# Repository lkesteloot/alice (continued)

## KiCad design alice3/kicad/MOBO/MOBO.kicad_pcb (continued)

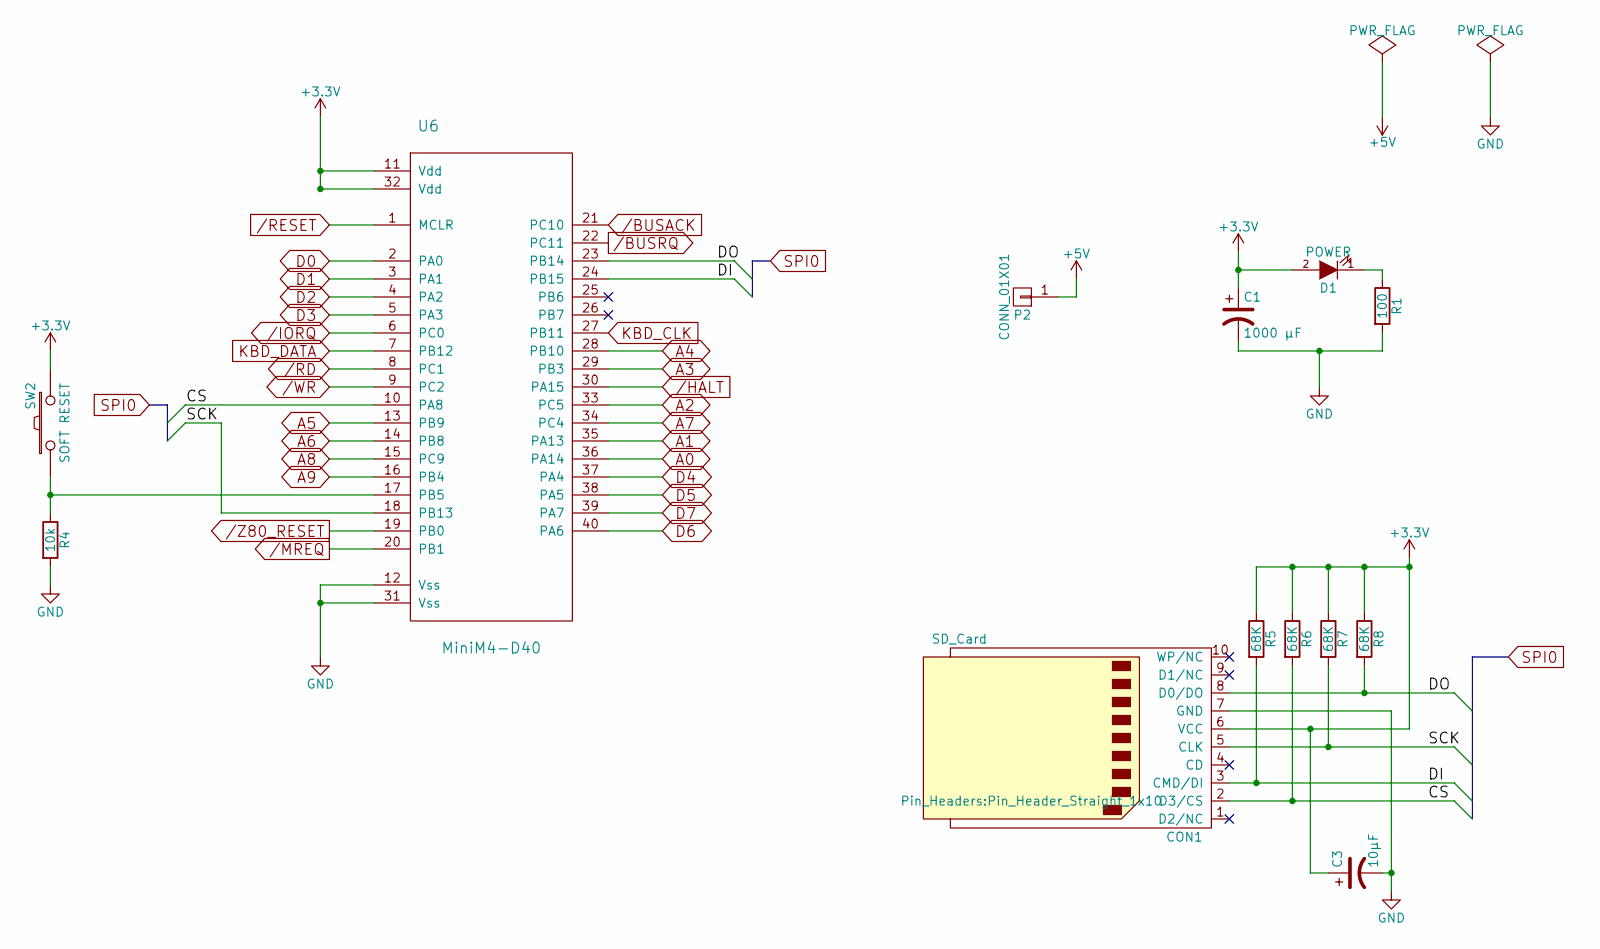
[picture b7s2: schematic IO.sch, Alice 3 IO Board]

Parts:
C1: 1000 µF; C_Radial_D8_L11.5_P3.5
C3: 10µF; C_Radial_D5_L11_P2.5
CON1: SD_Card; Pin_Header_Straight_1x10
D1: POWER; LED-5MM
P2: CONN_01X01; Pin_Header_Straight_1x01
R1: 100; Resistor_Horizontal_RM10mm
R4: 10k; Resistor_Horizontal_RM10mm
R5, R6, R7, R8: 68K; Resistor_Horizontal_RM10mm
SW2: SOFT RESET; SW_PUSH_SMALL
U6: MiniM4-D40; DIP-40_W15.24mm

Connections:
+5V: P2.1; also elsewhere on the board
/BUSACK: U6.21 (PC10); also elsewhere on the board
/BUSRQ: U6.22 (PC11); also elsewhere on the board
/HALT: U6.30 (PA15); also elsewhere on the board
/IO/CS: CON1.2 (D3/CS), R6.2, U6.10 (PA8)
/IO/DI: CON1.3 (CMD/DI), R5.2, U6.24 (PB15)
/IO/DO: CON1.8 (D0/DO), R8.2, U6.23 (PB14)
/IO/SCK: CON1.5 (CLK), R7.2, U6.18 (PB13)
/IORQ: U6.6 (PC0); also elsewhere on the board
/MREQ: U6.20 (PB1); also elsewhere on the board
/RD: U6.8 (PC1); also elsewhere on the board
/RESET: U6.1 (MCLR); also elsewhere on the board
/WR: U6.9 (PC2); also elsewhere on the board
/Z80_RESET: U6.19 (PB0); also elsewhere on the board
A0: U6.36 (PA14); also elsewhere on the board
A1: U6.35 (PA13); also elsewhere on the board
A2: U6.33 (PC5); also elsewhere on the board
A3: U6.29 (PB3); also elsewhere on the board
A4: U6.28 (PB10); also elsewhere on the board
A5: U6.13 (PB9); also elsewhere on the board
A6: U6.14 (PB8); also elsewhere on the board
A7: U6.34 (PC4); also elsewhere on the board
A8: U6.15 (PC9); also elsewhere on the board
A9: U6.16 (PB4); also elsewhere on the board
D0: U6.2 (PA0); also elsewhere on the board
D1: U6.3 (PA1); also elsewhere on the board
D2: U6.4 (PA2); also elsewhere on the board
D3: U6.5 (PA3); also elsewhere on the board
D4: U6.37 (PA4); also elsewhere on the board
D5: U6.38 (PA5); also elsewhere on the board
D6: U6.40 (PA6); also elsewhere on the board
D7: U6.39 (PA7); also elsewhere on the board
GND: C1.2, C3.2, CON1.7 (GND), R1.2, R4.2, U6.12 (Vss), U6.31 (Vss); also elsewhere on the board
KBD_CLK: U6.27 (PB11); also elsewhere on the board
KBD_DATA: U6.7 (PB12); also elsewhere on the board
unnamed: D1.1 (K), R1.1
unnamed: R4.1, SW2.1, U6.17 (PB5)

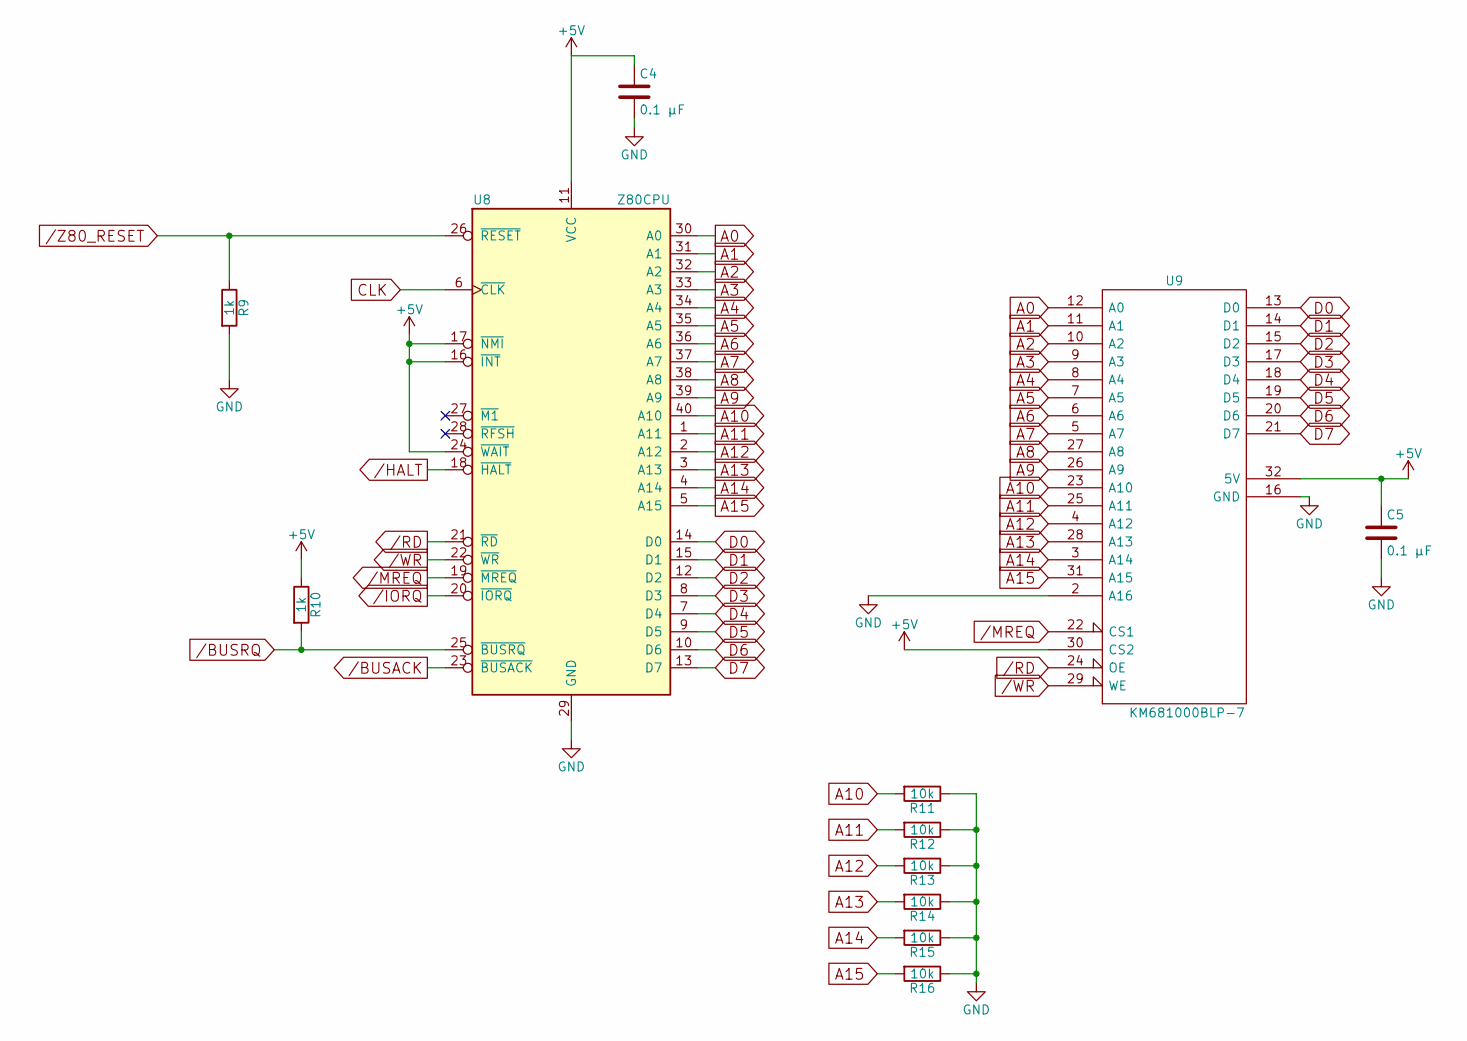
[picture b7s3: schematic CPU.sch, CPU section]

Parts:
C4, C5: 0.1 µF; C_Disc_D6_P5
R9, R10: 1k; Resistor_Horizontal_RM10mm
R11, R12, R13, R14, R15, R16: 10k; Resistor_Horizontal_RM10mm
U8: Z80CPU; DIP-40_W15.24mm
U9: KM681000BLP-7; DIP-32_W15.24mm

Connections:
/BUSACK: U8.23 (~BUSACK~); also elsewhere on the board
/BUSRQ: R10.2, U8.25 (~BUSRQ~); also elsewhere on the board
/HALT: U8.18 (~HALT~); also elsewhere on the board
/IORQ: U8.20 (~IORQ~); also elsewhere on the board
/MREQ: U8.19 (~MREQ~), U9.22 (CS1); also elsewhere on the board
/RD: U8.21 (~RD~), U9.24 (OE); also elsewhere on the board
/WR: U8.22 (~WR~), U9.29 (WE); also elsewhere on the board
/Z80_RESET: R9.1, U8.26 (~RESET~); also elsewhere on the board
A0: U8.30 (A0), U9.12 (A0); also elsewhere on the board
A1: U8.31 (A1), U9.11 (A1); also elsewhere on the board
A2: U8.32 (A2), U9.10 (A2); also elsewhere on the board
A3: U8.33 (A3), U9.9 (A3); also elsewhere on the board
A4: U8.34 (A4), U9.8 (A4); also elsewhere on the board
A5: U8.35 (A5), U9.7 (A5); also elsewhere on the board
A6: U8.36 (A6), U9.6 (A6); also elsewhere on the board
A7: U8.37 (A7), U9.5 (A7); also elsewhere on the board
A8: U8.38 (A8), U9.27 (A8); also elsewhere on the board
A9: U8.39 (A9), U9.26 (A9); also elsewhere on the board
A10: R11.2, U8.40 (A10), U9.23 (A10)
A11: R12.2, U8.1 (A11), U9.25 (A11)
A12: R13.2, U8.2 (A12), U9.4 (A12)
A13: R14.2, U8.3 (A13), U9.28 (A13)
A14: R15.2, U8.4 (A14), U9.3 (A14)
A15: R16.2, U8.5 (A15), U9.31 (A15)
CLK: U8.6 (~CLK~); also elsewhere on the board
D0: U8.14 (D0), U9.13 (D0); also elsewhere on the board
D1: U8.15 (D1), U9.14 (D1); also elsewhere on the board
D2: U8.12 (D2), U9.15 (D2); also elsewhere on the board
D3: U8.8 (D3), U9.17 (D3); also elsewhere on the board
D4: U8.7 (D4), U9.18 (D4); also elsewhere on the board
D5: U8.9 (D5), U9.19 (D5); also elsewhere on the board
D6: U8.10 (D6), U9.20 (D6); also elsewhere on the board
D7: U8.13 (D7), U9.21 (D7); also elsewhere on the board
GND: C4.2, C5.2, R9.2, R11.1, R12.1, R13.1, R14.1, R15.1, R16.1, U8.29 (GND), U9.2 (A16), U9.16 (GND); also elsewhere on the board

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
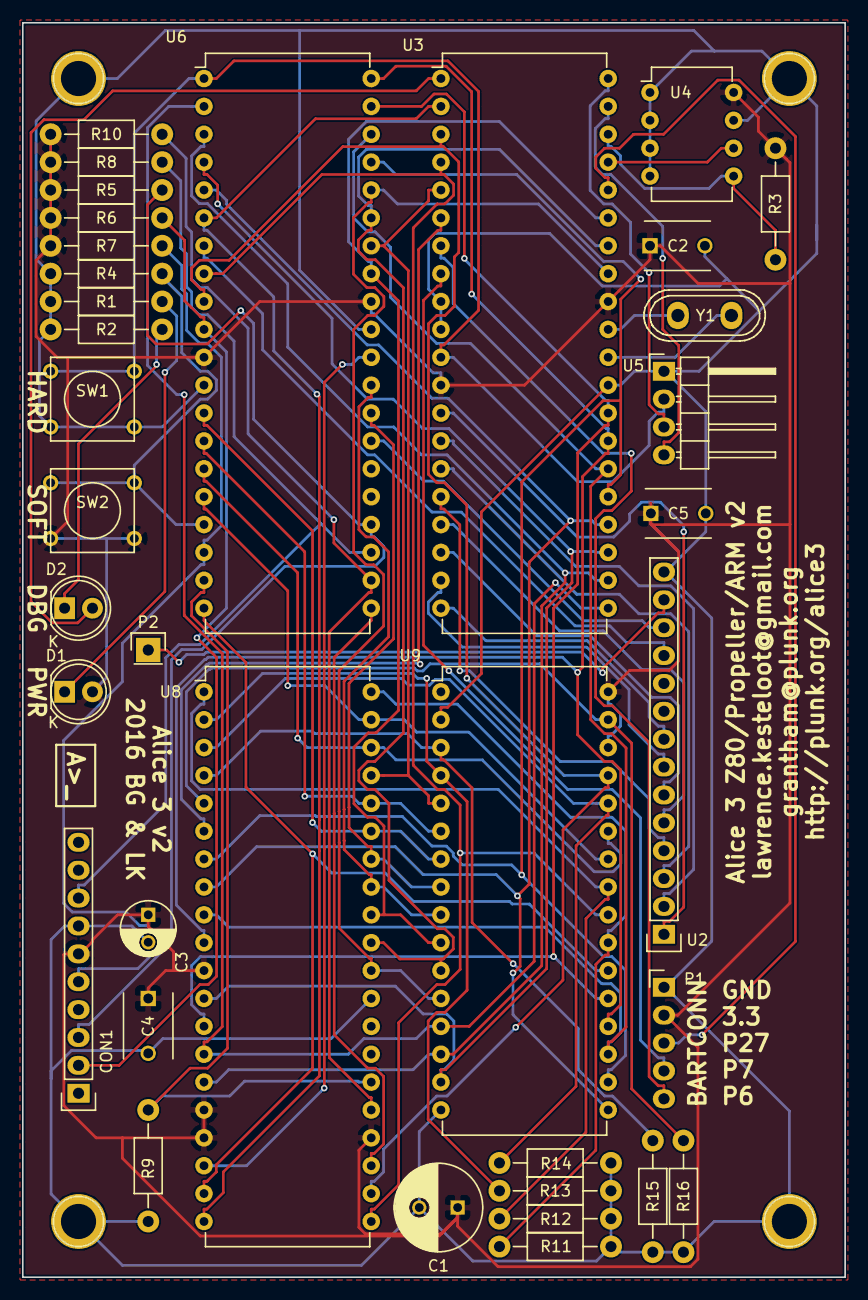
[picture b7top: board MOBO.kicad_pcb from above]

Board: 2 copper layers, 74.9 x 114.3 mm, 40 parts (0 on the bottom side), 64 nets.

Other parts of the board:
HOLE1, HOLE2, HOLE3, HOLE4: 1pin

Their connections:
GND: HOLE1.1, HOLE2.1, HOLE3.1, HOLE4.1; also elsewhere on the board

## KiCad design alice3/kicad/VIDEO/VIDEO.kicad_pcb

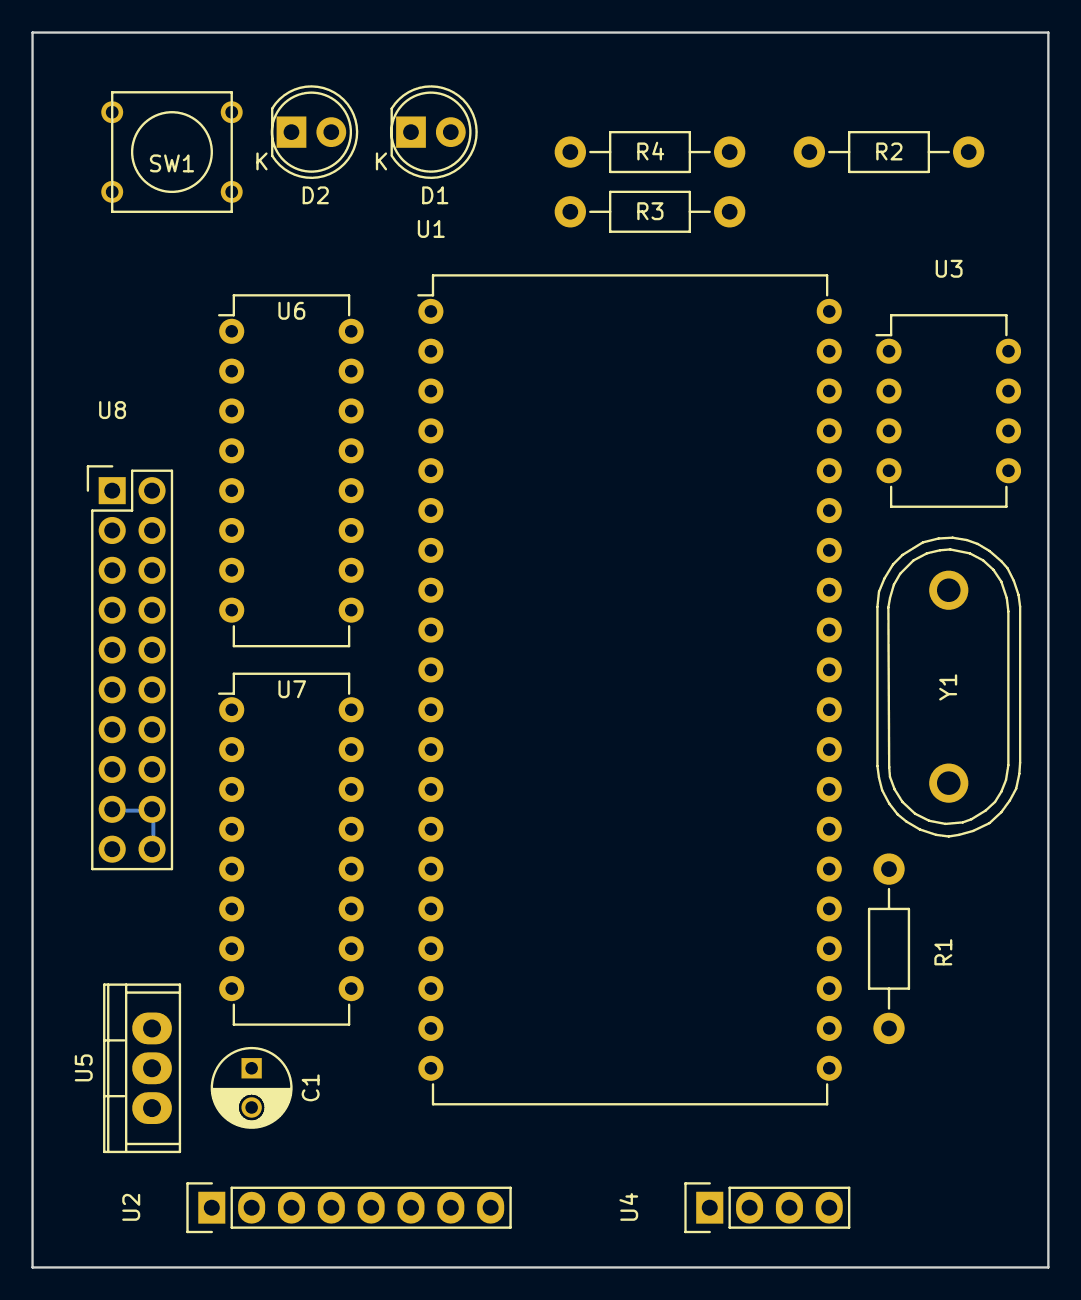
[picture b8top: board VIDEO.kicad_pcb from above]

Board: 2 copper layers, 64.8 x 78.7 mm, 17 parts (0 on the bottom side), 43 nets.

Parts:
C1: 1000 µF; C_Radial_D5_L6_P2.5
D1: POWER; LED-5MM
D2: DEBUG; LED-5MM
R1: 10K; Resistor_Horizontal_RM10mm
R2: 10k; Resistor_Horizontal_RM10mm
R3, R4: 100; Resistor_Horizontal_RM10mm
SW1: RESET; SW_PUSH_SMALL
U1: Propeller_P8X32A-D40; DIP-40_W25.4mm
U2: VGA_daughter_board; Pin_Header_Straight_1x08
U3: 24LC256; DIP-8_W7.62mm
U4: Propeller_Plug; Pin_Header_Straight_1x04
U5: LM2937-3.3; TO-220
U6, U7: 74HC4050; DIP-16_W7.62mm
U8: Alice_3_bus; Pin_Header_Straight_2x10
Y1: 5 MHz; Crystal_HC48-U_Vertical

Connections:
+3V3: C1.1, D1.2, R1.1, R2.1, U1.12, U1.32, U3.8, U5.3, U6.1, U7.1
+5V: U5.1, U8.2, U8.10
//IORQ: U1.33, U7.10
//WR: U1.34, U7.12
/A7: U1.35, U7.6
/D0: U1.21, U6.2
/D1: U1.22, U6.4
/D2: U1.23, U6.6
/D3: U1.24, U6.10
/D4: U1.25, U6.12
/D5: U1.26, U6.15
/D6: U1.27, U7.2
/D7: U1.28, U7.4
GND: C1.2, R3.2, R4.2, SW1.2, U1.9, U1.10, U1.29, U3.1, U3.2, U3.3, U3.4, U3.7, U4.1, U5.2, U6.8, U7.8, U7.14, U8.1, U8.20
unnamed: D1.1, R3.1
unnamed: D2.1, R4.1
unnamed: D2.2, U1.1
unnamed: R1.2, SW1.1, U1.11, U4.2
unnamed: R2.2, U1.38, U3.5
unnamed: U1.13, U2.1
unnamed: U1.14, U2.2
unnamed: U1.15, U2.3
unnamed: U1.16, U2.4
unnamed: U1.17, U2.5
unnamed: U1.18, U2.6
unnamed: U1.19, U2.7
unnamed: U1.20, U2.8
unnamed: U1.30, Y1.1
unnamed: U1.31, Y1.2
unnamed: U1.37, U3.6
unnamed: U1.39, U4.4
unnamed: U1.40, U4.3
unnamed: U6.3, U8.11
unnamed: U6.5, U8.12
unnamed: U6.7, U8.13
unnamed: U6.9, U8.14
unnamed: U6.11, U8.15
unnamed: U6.14, U8.16
unnamed: U7.3, U8.17
unnamed: U7.5, U8.18
unnamed: U7.7, U8.19
unnamed: U7.9, U8.9
unnamed: U7.11, U8.8

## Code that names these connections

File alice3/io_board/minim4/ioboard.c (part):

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#define KBD_BIT_COUNT 11

volatile short kbd_bits = 0;
volatile unsigned short kbd_data = 0;
volatile char up_key_flag = 0;
volatile char kbd_shift_status = 0;
volatile char kbd_alt_status = 0;
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        } else {
            queue_enq(&kbd_queue.q, (kbd_data >> 1) & 0xff);
        }
        kbd_data = 0;
        kbd_bits = 0;
    }
}
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#define MEMORY_DELAY_MICROS     10
#define IO_DELAY_MICROS     2

// IORQ, RD, WR, and A7 are specially implemented to be on one GPIO register
// in order to quickly determine if IO is being read or written

#define BUS_SIGNAL_CHECK_PORT GPIOC
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
        __asm__ volatile("" ::: "memory"); // Force all memory operations before to come before and all after to come after.

        while((BUS_SIGNAL_CHECK_PORT->IDR & BUS_RD_PIN_MASK) == BUS_RD_ACTIVE); /* busy wait for RD to rise */
        __asm__ volatile("" ::: "memory"); // Force all memory operations before to come before and all after to come after.
        BUS_set_DATA_as_input();

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
        __asm__ volatile("" ::: "memory"); // Force all memory operations before to come before and all after to come after.

        while((BUS_SIGNAL_CHECK_PORT->IDR & BUS_RD_PIN_MASK) == BUS_RD_ACTIVE); /* busy wait for RD to rise */
        __asm__ volatile("" ::: "memory"); // Force all memory operations before to come before and all after to come after.
        BUS_set_DATA_as_input();

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    HAL_NVIC_SetPriority(EXTI2_IRQn, 0, 0);
    HAL_NVIC_EnableIRQ(EXTI2_IRQn);

    // IORQ and A7 are port C pins 0, 4, as inputs
    GPIO_InitStruct.Pin = BUS_IORQ_PIN_MASK | BUS_A7_PIN_MASK;
    GPIO_InitStruct.Mode = GPIO_MODE_INPUT;
    GPIO_InitStruct.Pull = GPIO_NOPULL;
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#define RESET_BUTTON_IRQn EXTI9_5_IRQn
#define RESET_BUTTON_DELAY_MS 10

#define Z80_RESET_PORT GPIOB
#define Z80_RESET_PIN_MASK GPIO_PIN_0
#define Z80_RESET_ACTIVE 0
#define Z80_RESET_INACTIVE Z80_RESET_PIN_MASK
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    GPIO_InitStruct.Mode = GPIO_MODE_OUTPUT_PP;
    GPIO_InitStruct.Pull = GPIO_NOPULL;
    GPIO_InitStruct.Speed = GPIO_SPEED_FREQ_LOW;
    HAL_GPIO_Init(Z80_RESET_PORT, &GPIO_InitStruct); 
    HAL_GPIO_WritePin(Z80_RESET_PORT, Z80_RESET_PIN_MASK, Z80_RESET_ACTIVE);
    gZ80IsInRESET = 1;
}

void BUS_reset_start()
{
    HAL_GPIO_WritePin(Z80_RESET_PORT, Z80_RESET_PIN_MASK, Z80_RESET_ACTIVE);
    gZ80IsInRESET = 1;
    delay_ms(Z80_RESET_DURATION_MS);
}
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void BUS_reset_finish()
{
    gZ80IsInRESET = 0;
    HAL_GPIO_WritePin(Z80_RESET_PORT, Z80_RESET_PIN_MASK, Z80_RESET_INACTIVE);
}

volatile int gResetTheZ80 = 0;
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}

#define PROP_READY_PIN_MASK GPIO_PIN_14
#define PROP_READY_PORT GPIOC

void VIDEO_init()
{
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    GPIO_InitStruct.Mode = GPIO_MODE_INPUT;
    GPIO_InitStruct.Pull = GPIO_PULLUP;
    GPIO_InitStruct.Speed = GPIO_SPEED_FREQ_LOW;
    HAL_GPIO_Init(PROP_READY_PORT, &GPIO_InitStruct); 
}

void VIDEO_wait()
{
    int started = HAL_GetTick();
    int then = HAL_GetTick();
    while(HAL_GPIO_ReadPin(PROP_READY_PORT, PROP_READY_PIN_MASK)) {
        int now = HAL_GetTick();
        if(now - then > 500) {
            printf("Waited 500 more milliseconds for PROP_READY\n");
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
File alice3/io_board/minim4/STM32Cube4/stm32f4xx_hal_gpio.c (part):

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        pins).
  
    (#) The LSE oscillator pins OSC32_IN and OSC32_OUT can be used as general purpose 
        (PC14 and PC15, respectively) when the LSE oscillator is off. The LSE has 
        priority over the GPIO function.
  
    (#) The HSE oscillator pins OSC_IN/OSC_OUT can be used as 
        general purpose PH0 and PH1, respectively, when the HSE oscillator is off. 
        The HSE has priority over the GPIO function.
  
  @endverbatim
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
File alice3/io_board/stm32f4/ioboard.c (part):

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        } else if(strcmp(gMonitorCommandLine, "bus") == 0) {

            printf("RESET %s\n", HAL_GPIO_ReadPin(BUS_RESET_PORT, BUS_RESET_PIN_MASK) ? "high" : "low");
            printf("HALT %s\n", HAL_GPIO_ReadPin(BUS_HALT_PORT, BUS_HALT_PIN_MASK) ? "high" : "low");
            printf("IORQ %s\n", HAL_GPIO_ReadPin(BUS_IORQ_PORT, BUS_IORQ_PIN_MASK) ? "high" : "low");
            printf("MREQ %s\n", HAL_GPIO_ReadPin(BUS_MREQ_PORT, BUS_MREQ_PIN_MASK) ? "high" : "low");
            printf("RD %s\n", HAL_GPIO_ReadPin(BUS_RD_PORT, BUS_RD_PIN_MASK) ? "high" : "low");
            printf("WR %s\n", HAL_GPIO_ReadPin(BUS_WR_PORT, BUS_WR_PIN_MASK) ? "high" : "low");
            printf("BUSRQ %s\n", HAL_GPIO_ReadPin(BUS_BUSRQ_PORT, BUS_BUSRQ_PIN_MASK) ? "high" : "low");
            printf("BUSAK %s\n", HAL_GPIO_ReadPin(BUS_BUSAK_PORT, BUS_BUSAK_PIN_MASK) ? "high" : "low");

        } else if(strcmp(gMonitorCommandLine, "low128") == 0) {
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
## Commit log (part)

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2017-04-15 Fix various bugs in FIFO code.
2017-04-15 Can increment in memtool.
2017-04-15 Convert image to 32bits before accessing
2017-04-16 Pretty stable frame buffer.
2017-04-16 Double size of FIFO to avoid underrun.
2017-04-16 Encapsulate touchscreen in its own unit
2017-04-16 Add beginnings of events on hardware
2017-04-16 Add ERROR prints on unexpected conditions
2017-04-17 Move flush so gl.c is not dependent on network
2017-04-17 Add platform.mk file for choosing implementation
    Edit platform.mk to change the implementaiton of the rasterizer and events.
2017-04-17 More careful LCD pixel output.
2017-04-19 Convert output to G's
2017-04-24 Add second memory interface.
2017-04-24 Modify memtool to support 64-bit writes and reads.
2017-04-24 Protocol test program.
2017-04-24 Draw bounding box of triangle.
2017-04-24 Turn of debug printf and usleep() now that we block on swap buffers.
2017-04-25 Respect triangle color; display count of unhandled commands.
2017-04-25 Make GPU command buffer - not tested
2017-04-26 Correct check for mmap() failure (not compiled or tested).
2017-04-26 Change DEBUG_PRINT to undef
2017-04-27 Reset buffer after each frame.
2017-04-27 Put image in both framebuffers
    Make new put_image function.
    Put the fipImage in both framebuffers that may be scanned out.
    Center image correctly in dimensions less than the framebuffer size.
2017-04-27 Add a utility to save the framebuffers as images
    Save off each framebuffer using FreeImagePlus.
    FIP will automatically use an encoder matching the filename extension entered.
    e.g. sudo alice4save framebuffer0.png framebuffer1.jpg # not that you'd do this, but it works
    Hardcode the framebuffer location, rowbytes, and bpp for convenience.
2017-04-28 Spin triangle more slowly in the test.
2017-04-28 Disable networking in Arena, it doesn't compile on the embedded Linux.
2017-04-29 Bigger FB FIFO and latch the debug text.
2017-04-30 Compare open against -1 to detect failure
    OMG, this is kind of embarrassing.
2017-04-30 Fix tied evaluator record and read
    Fix cut-and-paste error in tied evaluator loop - set loop variable k but did not use it to read evaluator device
    Fix events_tie() - was not using the correct array index
2017-05-01 Software side of pattern.
2017-05-01 Add code to parse PATTERN (untested)
2017-05-01 Implement patterns in FPGA.
2017-05-02 Add pattern test to protocol program.
2017-05-02 Add optimization to all Makefiles
    This change boosts logo's CPU-only frame rate from 25 frames per second to 95.
2017-05-03 Double-buffer the command stream
    If "double_buffer_commands" is set to 0, commands are written directly to the GPU memory buffer for commands. (Therefore no additional commands can be safely written to the buffer until the GPU has f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
    If "double_buffer_commands" is set to 1, commands are written directly to a separate "staging" memory buffer. "swap" waits until any previous GPU work is complete, meaning the GPU buffer can be writt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
    N.B. By default now set double_buffer_commands to 1. It is a const variable me
2017-05-03 Expose front buffer bit.
2017-05-04 Add frame stats per-frame and averaged over a second
    PRINT_FRAME_STATS=1 will print ms for some portions of the frame every second.
    PRINT_FRAME_STATS=2 will print ms for some portions of the frame every frame.
2017-05-04 Program to pulse LCD backlight.
2017-05-04 Fix bounding box calculation.
2017-05-04 Modify fpgasim to do more efficient color interpolation.
2017-05-04 Print time spent waiting on raster finish
2017-05-04 Revert accidental change to platform makefile.
2017-05-04 Write overlay in single-bit red so as to not disturb the LCD. Need to investigate why this is necessary.
2017-05-05 add -lm for Linux build
2017-05-08 Tilt test over VNC
    Prints "TILT_VALID" and tilt valuators when tilt is within accurate ranges.
    Prints "TILT_INVALID" and does not print valuators when tilt is out of range.
2017-05-13 Add two stages to the reciprocal (from 4 to 6) to eliminate timing warnings.
    Fixes #34.
2017-05-17 Add modes for just ramp and for delaying all bits
    Change size to 800x480 so that output matches Alice 4 display
    - notably the ramp can be loaded into Alice 4 display to illustrate issues
    "make" creates all three images.
    Provide "--all8bits" to delay all 8 bits of the color, showing close to what Brad sees.
    Provide "--justramp" to output the color ramp with no output effect.
2017-05-18 Add Z buffer test to protocol.cpp.
2017-05-22 DISPLAY_ENABLE -> DATA_ENABLE
2017-05-22 Add some boards and chips we're using
    Adafruit Bluefruit LE SPI
    Adafruit L3GD20H breakout
    Adafruit PowerBoost 1000c
    STM STMPE811
2017-05-22 Add memory controller ports for Z.
2017-05-24 Add write FIFO and use it for color.
2017-05-24 Interpolate Z.
2017-05-24 Move i2c functions into utility module
2017-05-24 Accelerometer module
2017-05-24 Fix math error converting radians to degres
2017-05-24 Smooth accelerometer with exponential decay
    Add (current sensor reading * (1 - decay)) to (old * decay).
    Smoothing helps somewhat with decay = .5. Decay = .8 looks a lot better but loses rapid motion.
    Committing decay = 0.5.
2017-05-25 Clean up Verilog code.
2017-05-26 Fix Z buffer artifacts. Fixes #13.
2017-05-26 Add stats to protocol test.
2017-05-26 Clear Z in protocol test.
2017-05-28 Remove test code.
2017-05-28 Add notes for test fifo.
2017-05-29 Speed up rasterization. Fixes #40.
2017-05-29 Fix use of fifo.empty in read fifo.
2017-06-02 Always spin object slowly, fix Z
    Remove call to gversion and machine-dependent Z setup.
    Use default Z function, back-to-front values for lsetdepth, and clear Z to far.
    Set "spin" to default to TRUE and spin 1/3 as fast as it was spinning.
2017-06-03 Add tilt
2017-06-04 Rasterize lines
2017-06-04 Rasterize lines more correctly
    Draw boxes that represent lines by extending line by linewidth along
    axis perpendicular to the line's major axis, resulting in parallelograms.
2017-06-04 Factor out libawesome.
2017-06-04 Add home support to protocol test program.
2017-06-04 Use one global Awesome
    Move struct definition into awesome.c.
    Keep one global Awesome instance in awesome.c.
    Remove all Awesome pointers from awesome functions.
    Fixup protocol test to match.
2017-06-04 Don't pass a pointer to an Awesome
2017-06-04 Warn if we skip a frame.
2017-06-04 Add Arena
2017-06-04 compile with networking
2017-06-04 Implement czclear(), fix #39
    Implement czclear in rasterizer interface and rasterizer implementations.
    In hardware_rasterizer, pass czclear to libawesome
    Use czclear in logo and jello (already used in bounce)
2017-06-04 Set ESC (Home) to exit only submenus in buttonfly
2017-06-04 Add ability to dump logo commands to a file. For #22.
2017-06-04 Add Make target for writing logo.bin to SD card.
2017-06-05 Add memory thrashing tool.
2017-06-11 Fix line endings for u-boot.txt.
2017-06-12 Re-enable double buffering of commands.
2017-06-12 Break up long thin triangles. For issue #17.
    Long thin (diagonal) triangles waste a lot of time in the
    rasterizer because we consider every point in the bounding
    box. With this change, if the ratio of triangle pixels
    to bounding box pixels is low, we tesselate the triangle.
    This halves the number of bounding box pixels (1.8m to 0.9m)
    at the slowest frame of buttonfly. (The bevel of the button
2017-06-12 Configure extra memory ports.
2017-06-16 add network events example in a comment
2017-06-16 fix array overrun
2017-06-16 Avoid divide by zero when displaying statistics.
2017-06-16 Don't start reading command buffer until we're ready.
2017-06-16 Bogus no-op changes by Quartus.
2017-07-15 Update overview page.
2017-07-15 Fix up Alice 2 docs.
2017-07-15 Load fonts over https.
2017-07-15 Use arabic numerals instead of roman ones for Alice version numbers.
2017-07-15 Add stub Alice 4 page.
2017-07-20 Disable blinking LED.
2017-07-26 Don't show arena instructions. Fixes #58.
2017-07-26 Add disabled code to split up lines.
2017-08-02 Add Makefile targets to start/stop service.
2017-08-03 IrisGL transformation and lighting benchmark
2017-08-04 Don't enable shutdown in Makefile.
2017-08-04 Dummy events in platform Makefile.
2017-08-05 Fix aspect ratio of ideas.
2017-08-05 Replace shutdown with ideas.
2017-08-06 Final flight changes to make it build.
2017-08-06 Fix flight warnings and clear bug in gl.
2017-08-08 Run the 747 by default in flight.
2017-08-09 Link to web page.
2017-08-09 Add secret menu.
2017-08-10 switch interaction to that of jello
2017-08-10 render all 6 walls with faceculling
2017-08-15 Big VCF West 2017 commit
    Terminal.spin: complete rewrite in prop asm, lots more codes handled,
    jump table used which should provide a good example for streamlining in
    the future
    Bus_interface.spin: better documentation at the top, added serial terminal
    mirroring but commented-out, added ay_allatonce handler, added ay_BEL
    Main.spin: added another row to the buffer for easier terminal scrolling
2017-08-15 Added JDCogSerial.spin to alice3/video_board/propeller directory since the alternative commented-out terminal code in Main.spin references it
2017-08-16 make CE2 high
2017-08-16 draft DABO2 PCB
2017-08-16 footprints
2017-08-17 increase SD speed to about 21MHz after init
2017-08-17 ARM fimware binary with faster SD access
2017-08-19 catch correct enum for WRITE_DMA
2017-08-19 implement ARM firmware for DMA READ and WRITE
2017-08-26 set up RFSH and WAIT signals correctly
2017-08-28 1st set MOBO schematic fixes for 1st PCBWay spin
    Various fixes for KiCAD messing up components
    Button on BOOT0
    No huge cap on power supply LED
    Discard RAM
    Route ARM to Z80 /WAIT and /RFSH
    Use "~" for active-low lines (shown in schematic by line above them)
2017-08-29 V4 improvements round 2
    Label buttons, LEDs, and connectors
    Delete footprints for deleted schematic parts
    Move microUSB jack and space out PS2, VGA connectors
    Position SMT Propeller crystal
    Change BOOT0 header to button
    Delete RAM
2017-08-29 consolidate all Z80 addr pins on one ARM port
2017-09-06 fix misspelling of "staging"
2017-09-07 constant current part FAN5333A/B
2017-09-07 integrate constant current driver, drop TFT Friend
2017-09-08 replace L3DG20H breakout with actual chip
2017-09-09 TPS61090 boost supply
2017-09-10 add source files for components
2017-09-11 run LIPO to STMPE811 ADC on IN0
2017-09-13 Add link to red button.
2017-09-13 Acrylic enclosure.
2017-09-13 l3gd20h qfn footprint
2017-09-13 first draft of layout
2017-09-14 add hidden PAD pins that are GND
2017-09-14 Second draft of layout
    Lawrence fixes to schematic
    Layout PCB
2017-09-16 remove R pulling PWREN to VBAT
2017-09-17 one more draft layout; better 3v3 plane
2017-09-18 add SMD 1206 testpoint pad footprint
2017-09-18 Hopefully near final layout
2017-09-27 Add jac library including large hole
2017-09-29 add ideas
2017-09-29 rotate 180 degrees
2017-10-10 Fix up WaveDrom for write FIFO.
2017-10-12 Minor tweaks to write-up.
2017-10-16 Better motivation for area reciprocal.
2017-10-16 Get flight to compile on Alice 4.
2017-10-16 Slower accelerator decay.
2017-10-16 Fix secret menu.
2017-10-16 Re-enable culling, implement correctly
    Ideas now works and the bounce models (except for doughnut?!) work properly and at full rate
2017-10-22 Start Verilator simulation integration.
2017-10-22 Add Frame buffer to Verilator.
2017-10-24 Add and link placeholder for libgl page
2017-10-25 Add more about libgl and the platform files
2017-10-25 Fix FPG to FPGA
2017-11-09 Undo accidental change to secret menu in buttonfly.
2017-11-09 Can exit flight with Esc key.
2017-11-09 Better accelerometer for jello.
2017-11-09 Add gyro library.
2017-11-09 Use accelerometer to move insect.
2017-11-19 Added tools page.
2017-11-19 In-progress sim work.
2017-11-27 Fix apostrophes.
2017-12-03 Add Grant Searle's BASIC + Alice 3 changes
2017-12-03 add Makefile
2017-12-06 Add tool to convert zasm .lst to az80 .prn for simualtor symbols
2018-01-04 Fix incorrectly rendered models in bounce
    I previously added backface in global initialization past to prevent
    the frontmost faces of the box from being rendered. Some of the
    models don't render properly with backface(TRUE). So enable backface
    only for the box.
2018-02-08 Remove remaining continue in libgl
    https://www.teamten.com/lawrence/programming/avoid-continue.html
2018-02-27 Sim: Don't modify internal signals, only modify top parameters.
2018-02-27 Sim: Go back to full-screen buffer.
2018-02-27 Sim: Simulate command buffer.
2018-02-28 Sim: Draw test triangle.
2018-03-03 Add NOTES file about binary command stream file.
2018-04-27 Minor tweaks to docs.
2018-05-06 Fix up XXX comments.
2018-05-24 Clarify members page.
2018-05-24 Yet more members formatting.
2018-06-06 Remove VNC library
2018-10-13 NASCOM BASIC does not support "ELSE" clauses on "IF" statements. Some lines were still too long. Fixed some semantic errors introduced by breaking long lines earlier.
2019-03-16 Embed YouTube videos of Alice 4 presentation.
